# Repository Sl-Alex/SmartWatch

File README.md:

# General description
This project aims to create an open-source smartwatch with the following functionality:
- 1.3" OLED display (bright enough to work in outdoor conditions)
- BLE module (HM-10), pin-to-pin compatibility with well-known HC-06
- small vibration motor (SMS/Call notifications and so on)
- STM32F103CBT6 microcontroller.
- Big external SPI flash memory (M25P40), SW OTA update and a lot of images can be stored there.
- BMC150 accelerometer/compass (can recognize double tap on the screen).
- BMP180 barometer/thermometer (just because there is a plenty of space).
- 320mAh battery allowing up to 3 weeks standby time (with BLE active).
- PCB size: 37*25, complete assembled height should be about 10mm.
- 3D models for all parts are in my [KiCAD_libs](https://github.com/Sl-Alex/KiCAD_libs) repository, case will be available a bit later, so the whole project can be easily reproduced.

# Hardware
Both schematic and PCB were created with KiCAD. KiCAD project is located in the PCB subfolder. Project uses components from my [KiCAD_libs](https://github.com/Sl-Alex/KiCAD_libs) repository.<br />
**Status**: Finished. PCB is assembled, all HW features are tested and work as expected. Standby time seems to be about 3 weeks (with BLE active).

# Software
Project is created in [EmBitz](https://www.embitz.org/)<br />
**Status**: Can be used on a daily basis with some basic functionality (automatic date/time synchronization, SMS reception). Feel free to submit patches, create or discuss issues [here](https://github.com/Sl-Alex/SmartWatch/issues).<br />

# Licensing
The whole project is available under GPL v3 license (see [LICENSE](LICENSE) file), except of files, which clearly mention other license type in the file header.

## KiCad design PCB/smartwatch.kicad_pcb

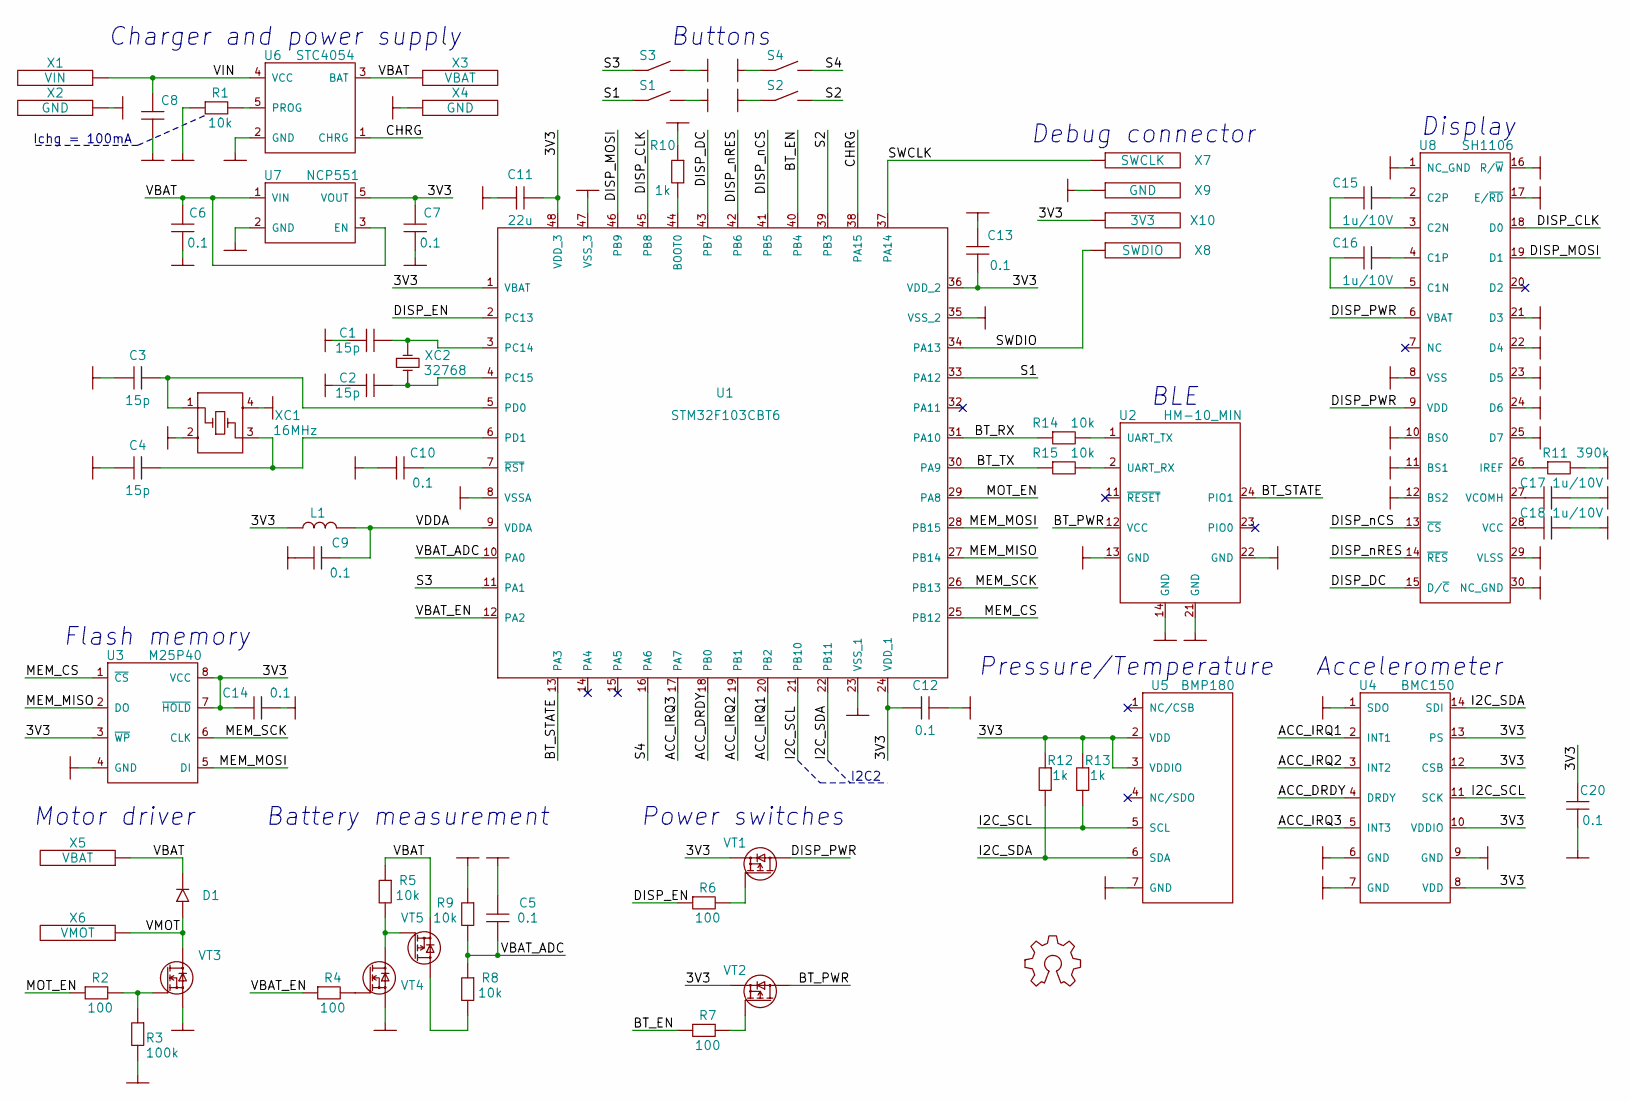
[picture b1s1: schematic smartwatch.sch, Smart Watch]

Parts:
C1, C2, C3, C4: 15p; 0402_C
C5, C6, C7, C9, C10, C12, C13, C14, C20: 0.1; 0402_C
C8: capacitor; 0402_C
C11: 22u; 0603_C
C15, C16, C17, C18: 1u/10V; 0603_C
D1: diode; SOD523
L1: inductor; 0603_L
LG?1: LOGO; OSHW
R1, R5, R8, R9, R14, R15: 10k; 0402_R
R2, R4, R6, R7: 100; 0402_R
R3: 100k; 0402_R
R10, R12, R13: 1k; 0402_R
R11: 390k; 0402_R
S1, S2, S3, S4: button_NO; B3U3000P
U1: STM32F103CBT6; LQFP48
U2: HM-10_MIN
U3: M25P40; SO8
U4: BMC150; LGA14
U5: BMP180; LGA7
U6: STC4054; SOT23-5
U7: NCP551; SOT23-5
U8: SH1106; UG-2864HSWEG01
VT1, VT2, VT5: MOSFET_P_DGS; PQFN2x2
VT3, VT4: MOSFET_N_DGS; PQFN2x2
X1: VIN; SLD_POINT
X2, X4, X9: GND; SLD_POINT
X3, X5: VBAT; SLD_POINT
X6: VMOT; SLD_POINT
X7: SWCLK; SLD_POINT
X8: SWDIO; SLD_POINT
X10: 3V3; SLD_POINT
XC1: 16MHz; SMD_3225
XC2: 32768; SMD_3215

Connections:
/3V3: C7.2, C11.1, C12.1, C13.1, C14.2, C20.2, L1.1, R12.1, R13.1, U1.1 (VBAT), U1.24 (VDD_1), U1.36 (VDD_2), U1.48 (VDD_3), U3.3 (~WP), U3.7 (~HOLD), U3.8 (VCC), U4.8 (VDD), U4.10 (VDDIO), U4.12 (CSB), U4.13 (PS), U5.2 (VDD), U5.3 (VDDIO), U7.5 (VOUT), VT1.3 (S), VT2.3 (S), X10.1
/ACC_DRDY: U1.18 (PB0), U4.4 (DRDY)
/ACC_IRQ1: U1.20 (PB2), U4.2 (INT1)
/ACC_IRQ2: U1.19 (PB1), U4.3 (INT2)
/ACC_IRQ3: U1.17 (PA7), U4.5 (INT3)
/BT_EN: R7.1, U1.40 (PB4)
/BT_PWR: U2.12 (VCC), VT2.1 (D)
/BT_RX: R14.1, U1.31 (PA10)
/BT_STATE: U1.13 (PA3), U2.24 (PIO1)
/BT_TX: R15.1, U1.30 (PA9)
/CHRG: U1.38 (PA15), U6.1 (CHRG)
/DISP_CLK: U1.45 (PB8), U8.18 (D0)
/DISP_DC: U1.43 (PB7), U8.15 (D/~C)
/DISP_EN: R6.1, U1.2 (PC13)
/DISP_MOSI: U1.46 (PB9), U8.19 (D1)
/DISP_PWR: U8.6 (VBAT), U8.9 (VDD), VT1.1 (D)
/DISP_nCS: U1.41 (PB5), U8.13 (~CS)
/DISP_nRES: U1.42 (PB6), U8.14 (~RES)
/I2C_SCL: R13.2, U1.21 (PB10), U4.11 (SCK), U5.5 (SCL)
/I2C_SDA: R12.2, U1.22 (PB11), U4.14 (SDI), U5.6 (SDA)
/MEM_CS: U1.25 (PB12), U3.1 (~CS)
/MEM_MISO: U1.27 (PB14), U3.2 (DO)
/MEM_MOSI: U1.28 (PB15), U3.5 (DI)
/MEM_SCK: U1.26 (PB13), U3.6 (CLK)
/MOT_EN: R2.1, U1.29 (PA8)
/S1: S1.1, U1.33 (PA12)
/S2: S2.2, U1.39 (PB3)
/S3: S3.1, U1.11 (PA1)
/S4: S4.2, U1.16 (PA6)
/SWCLK: U1.37 (PA14), X7.1
/SWDIO: U1.34 (PA13), X8.1
/VBAT: C6.1, D1.2, R5.1, U6.3 (BAT), U7.1 (VIN), U7.3 (EN), VT5.3 (S), X3.1, X5.1
/VBAT_ADC: C5.2, R8.1, R9.2, U1.10 (PA0)
/VBAT_EN: R4.1, U1.12 (PA2)
/VDDA: C9.2, L1.2, U1.9 (VDDA)
/VIN: C8.2, U6.4 (VCC), X1.1
/VMOT: D1.1, VT3.1 (D), X6.1
GND: C1.1, C2.1, C3.1, C4.1, C5.1, C6.2, C7.1, C8.1, C9.1, C10.1, C11.2, C12.2, C13.2, C14.1, C17.2, C18.2, C20.1, R1.1, R3.2, R9.1, R10.1, R11.2, S1.2, S2.1, S3.2, S4.1, U1.8 (VSSA), U1.23 (VSS_1), U1.35 (VSS_2), U1.47 (VSS_3), U2.13 (GND), U2.14 (GND), U2.21 (GND), U2.22 (GND), U3.4 (GND), U4.1 (SDO), U4.6 (GND), U4.7 (GND), U4.9 (GND), U5.7 (GND), U6.2 (GND), U7.2 (GND), U8.1 (NC_GND), U8.8 (VSS), U8.10 (BS0), U8.11 (BS1), U8.12 (BS2), U8.16 (R/~W), U8.17 (E/~RD), U8.21 (D3), U8.22 (D4), U8.23 (D5), U8.24 (D6), U8.25 (D7), U8.29 (VLSS), U8.30 (NC_GND), VT3.3 (S), VT4.3 (S), X2.1, X4.1, X9.1, XC1.2 (NC), XC1.4 (NC)
unnamed: C1.2, U1.3 (PC14), XC2.1
unnamed: C2.2, U1.4 (PC15), XC2.2
unnamed: C3.2, U1.5 (PD0), XC1.1
unnamed: C4.2, U1.6 (PD1), XC1.3
unnamed: C10.2, U1.7 (~RST)
unnamed: C15.1, U8.3 (C2N)
unnamed: C15.2, U8.2 (C2P)
unnamed: C16.1, U8.5 (C1N)
unnamed: C16.2, U8.4 (C1P)
unnamed: C17.1, U8.27 (VCOMH)
unnamed: C18.1, U8.28 (VCC)
unnamed: R1.2, U6.5 (PROG)
unnamed: R2.2, R3.1, VT3.2 (G)
unnamed: R4.2, VT4.2 (G)
unnamed: R5.2, VT4.1 (D), VT5.2 (G)
unnamed: R6.2, VT1.2 (G)
unnamed: R7.2, VT2.2 (G)
unnamed: R8.2, VT5.1 (D)
unnamed: R10.2, U1.44 (BOOT0)
unnamed: R11.1, U8.26 (IREF)
unnamed: R14.2, U2.1 (UART_TX)
unnamed: R15.2, U2.2 (UART_RX)

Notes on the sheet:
Motor driver
Battery measurement
Power switches
Pressure/Temperature
Accelerometer
BLE
Display
Flash memory
Charger and power supply
Buttons
Debug connector
Ichg = 100mA
I2C2

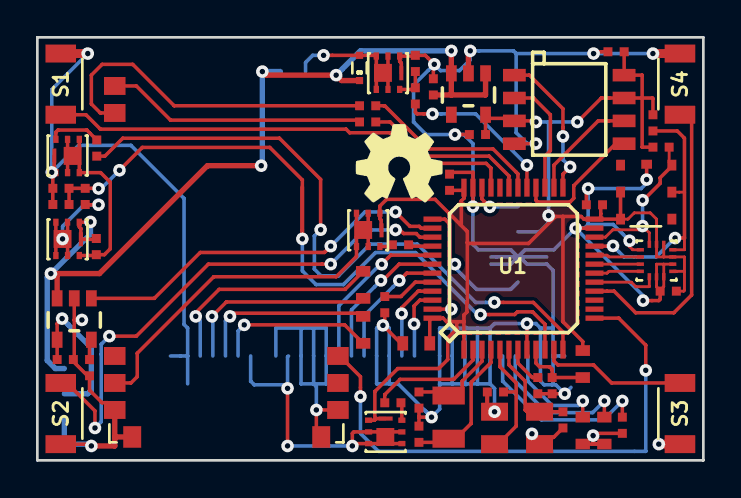
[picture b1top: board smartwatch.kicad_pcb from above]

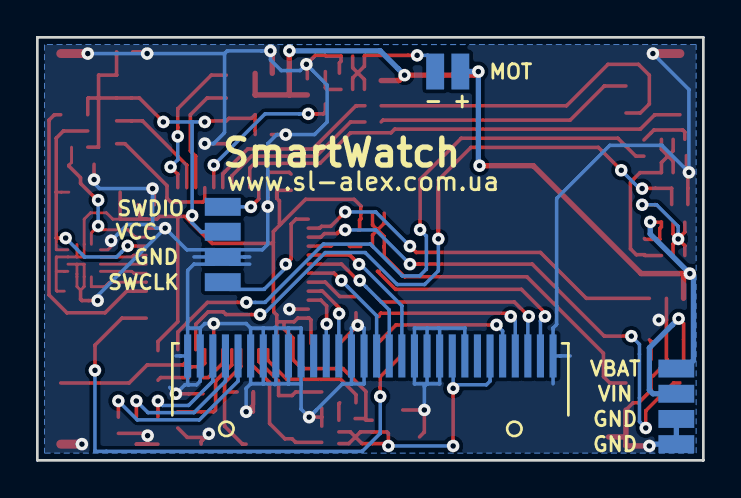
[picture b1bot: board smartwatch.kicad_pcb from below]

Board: 2 copper layers, 37.0 x 23.5 mm, 66 parts (11 on the bottom side), 60 nets.

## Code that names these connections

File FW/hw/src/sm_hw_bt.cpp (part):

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#include "sm_hal_gpio.h"
#include "sm_hal_rcc.h"

#define BT_RX_PORT  GPIOA_BASE
#define BT_RX_PIN   10
#define BT_TX_PORT  GPIOA_BASE
#define BT_TX_PIN   9
#define BT_EN_PORT  GPIOB_BASE
#define BT_EN_PIN   4
#define BT_ST_PORT  GPIOA_BASE
#define BT_ST_PIN   3

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    mTextSize = 0;
    mDataSize = 0;
#ifndef PC_SOFTWARE
    mPowerPin = new SmHalGpio<BT_EN_PORT, BT_EN_PIN>();
    mPowerPin->setModeSpeed(SM_HAL_GPIO_MODE_OUT_PP, SM_HAL_GPIO_SPEED_2M);

    mRxPin = new SmHalGpio<BT_RX_PORT, BT_RX_PIN>();
    mTxPin = new SmHalGpio<BT_TX_PORT, BT_TX_PIN>();

    mRxPin->setModeSpeed(SM_HAL_GPIO_MODE_IN_FLOAT, SM_HAL_GPIO_SPEED_2M);
    mTxPin->setModeSpeed(SM_HAL_GPIO_MODE_AF_PP, SM_HAL_GPIO_SPEED_2M);
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
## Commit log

2016-04-11 Draft PCB is added
2016-04-11 README update
2016-04-20 First iteration (only SH1106 and some GUI classes work fine)
2016-04-21 SPI Flash nWR is connected to 3V3
2016-04-21 SPI flash initial support (yet TBD) GUI improvements
2016-04-24 External flash update
2016-04-24 Useless file is removed
2016-04-25 "Slow" flash bugfix, small cleanup.
2016-05-03 PCB (everything is done, should be checked)
2016-05-03 PCB: Preparing production files
2016-05-04 Minor update and final production files for seeedstudio.
2016-06-04 Values update
2016-06-08 Update README.md
    Readability improvements
2016-06-08 GPIO class, draft SW SPI and display classes
2016-06-08 PCB component values update
2016-06-09 Display now depends only on SmHwAbstractSpi and SmHwGpioPin
2016-06-09 GPIO abstraction and template
2016-06-09 HW SPI class (templated, based on SmHwAbstractSpi)
2016-06-09 HW SPI enable. RCC will be implemented in a separate class.
2016-06-09 RCC clocking control, display power control
2016-06-09 Bugfixes (wrong pointer, wrong loop iterator)
2016-06-09 HW and SW SPI bugfixes
2016-06-10 SmHwSysTimer first prototype
2016-06-12 This closes #1 (system timer)
2016-06-12 Buttons draft
2016-06-12 Removing old display and GPIO drivers
2016-06-12 Battery measurement draft
2016-06-12 SmHwBattery singleton (with automatic update)
2016-06-13 Starting #4
2016-06-13 Skeleton for #3 (SPL - independent storage class)
2016-06-13 Removing obsolete SmartStorage, it will be replaced by SmHwStorage class (see #3)
2016-06-13 Closes #3 (Storage implementation)
2016-06-13 Closes #2 (all values are mentioned)
2016-06-14 Power manager skeleton, will be implemented in the next commits. See #7
2016-06-14 SmHwPowerMgr (#7) update
2016-06-14 Update README.md
    Add licensing information
2016-06-14 Update README.md
    Fix URL
2016-06-14 Updating SmHwPowerMgr (#7)
2016-06-14 SPL is completely removed
2016-06-14 License update (SPL is not used)
2016-06-14 SmHwPowerMgr (#7) draft implementation. Should be checked with the hardware.
2016-06-14 This closes #7 (power manager)
2016-06-14 Correct display sleep/wake
2016-06-15 This closes #8 (keyboard is implemented instead of separate buttons)
2016-06-16 Adding missing keyboard files
2016-06-16 ADC and SPI flash power management implementation, SmHalSysTimer bugfix
2016-06-17 Removing obsolete "font.c"
2016-06-17 Minor update
2016-06-20 BMC150 wake on double tap (very draft, but works)
2016-07-15 GUI classes rework
2016-07-15 Closes #10 (migration to 128kB flash)
2016-07-16 Documentation
2016-07-16 More documentation
2016-07-25 More documentation, storage class update
2016-07-25 Final SmFont concept, ready to implement
2016-07-27 Flash Packer skeleton
2016-07-27 Flash packer: get correct file list
2016-07-27 Flash packer update
2016-07-27 Flash packer update. Supports BIN and PBM files.
2016-07-28 Bugfix for #15 (to be verified with a HW)
2016-07-28 Flash packet Linux version modifications
2016-07-28 This closes #15. CRC32 calculation is also updated.
2016-07-28 Solving I2C reinitializing issue.
2016-07-29 Next documentation pack (see #11)
2016-07-29 This is the last documentation commit. Closing #11
2016-07-30 This closes #12. Minor code style fixes.
2016-07-31 Flash packer (#14) and SmFont (#13) update.
2016-08-05 This commit closes #14. Now flash packer does everything we need
2016-08-05 This closes #13 (Printing strings with SmFont)
2016-08-05 Adding hints for the sm_strings template
2016-08-06 Removing sm_strings.h, it will be generated by flash packer. Documentation
2016-08-10 Update for #21 (GUI testing with QT) and #17 (FW Resources)
2016-08-10 This closes #19 (Keyboard events)
2016-08-10 Keyboard and system timer can be emulated in QT test software
2016-08-20 Flash packer bug fix, schematic update, complete Ukrainian letters support
2016-09-21 Adding charge icons, removing update.bin
2016-09-21 Battery enhancement
2016-09-22 Charge status and battery icons on the desktop
2016-09-22 BT signal icons and basic icons handling in SmDesktop
2016-09-22 FW build fix
2016-09-28 This is an update for #23 (letter spacing implementation). Letter spacing is the very first number in the *.txt file.
2016-09-28 Letter spacing documentation
2016-09-28 This closes #24 (ASCII text support)
2016-09-28 Draft SmDesktop, RTC wrapper and 7-segment font.
2016-10-02 Updates for #22 (Charge status) and #20 (RTC wrapper).
2016-10-03 This closes #22 (charge status)
2016-10-09 This closes #20 (RTC wrapper)
2016-10-20 This closes #27 (SmAnimator enhancement)
2016-10-20 This closes #26 (string width calculation)
2016-10-21 SmMainMenu draft (with animation), SmAnimator bugfixes and improvements, many minor improvements
2016-10-22 Main menu with animations
2016-10-26 This closes #17 (main menu), updates #28 (editors)
2016-10-27 This closes #29 (power on and off symbols). This closes #28 (editors). This updates #16 (menus).
2016-10-27 Menus update (#16)
2016-10-28 Moving CMSIS and MCU headers to "thirdparty" folder
2016-10-28 Updating "thirdparty" folder
2016-10-29 This closes #16, closes #30.
2016-10-29 This closes #25. Should be checked with a HW.
2016-11-19 This closes #35 (power management bug), closes #37 (extend onWake)
2016-11-19 Minor style improvement
2016-11-20 RTC alarm bugfix, emulator update
2016-11-20 Wake IRQs fix
2016-11-22 SmHwBt protocol early draft (#31) Will work also in emulator (with HM-10 via serial port)
2016-11-23 SmHwBt improvements (#31)
2016-11-24 This closes #31 (BT communication protocol)
2016-11-25 Removing codecvt dependency (#39). Must be tested under Linux
2016-11-25 Documentation improvements
2016-11-25 This closes #38 (BT communication)
2016-11-25 sm_strings.tpl documentation improvement
2016-11-28 Strings template fix
2016-11-28 AHB peripheral is added
2016-11-28 Update for #33 (date/time synchronization) CRC32 is yet to be calculated and verified.
2016-11-29 CRC32 for BT reception
2016-11-30 SmHalRtc PC version improvements
2016-11-30 Documentation, minor improvements
2016-12-04 First early draft Android app (does not work at all)
2016-12-04 Removing obsolete files
2016-12-06 Menu layout
2016-12-07 Update for #34 (Android software) Draft fragments are implemented, fragment switching works.
2016-12-11 Extendind SmCenter template (#34)
2016-12-20 Further SmCenter improvements
2017-01-30 Updating #34 (very draft BLE implementation, not usable yet)
2017-02-01 Updating #34 (Connect/Send/Disconnect functionality seems to work, Read will follow)
2017-02-02 Closing #44, updating #34. BLE works now (see SmWatchService example)
2017-02-05 Updating #34 (FW version request)
2017-02-06 SmartWatch emulator improvements
2017-02-06 Updating #34 (DateTime sync)
2017-02-09 BT UART DMA send implementation
2017-02-23 This updates #46 (simple SMS notification)
2017-02-28 This closes #48 (SmHwMotor notifications) and updates #46 (simple SMS notification)
2017-02-28 This closes #46 (simple SMS notification), closes 36 (draft Android SW)
2017-03-01 This closes #36 (documentation)
2017-03-01 Fix compile error on Windows
2017-03-01 This closes #50 (Digits animation)
2017-03-03 Preparation for #49 (complete notification)
2017-03-03 Bootloader draft (#32), Complete notification draft (#49)
2017-03-03 Complete notification update (#49)
2017-03-04 BLE connection should be reliable now (#54). Small code cleanup was done.
2017-03-04 This closes #49 (complete notification)
2017-03-05 Extended timeout for notifications, asking for permissions, adding missing files.
2017-03-06 This closes #51 (version string is loadable from external flash). Minor stability improvements
2017-03-07 Time will be synchronized on both time and timezone change
2017-03-08 This closes #54 (BLE connection fails)
2017-03-08 This closes #41 (About screen)
2017-03-08 Notification sleep timeout update, README update
2017-03-11 This closes #56 (Show RSSI value), updates #57 (log implementation)
2017-03-12 datetime and log fix
2017-03-12 This closes #58 (battery measurement)
2017-03-12 Speeding up about fragment, minor fixes
2017-03-13 Minor fix
2017-03-21 This closes #61
